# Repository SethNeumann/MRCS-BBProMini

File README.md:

# MRCS-BBProMini
## License: Creative Commons Attribution-NonCommercial-ShareAlike

A ProMini in a BBLeo form factor for use on MRCS cpNode

Initial proof of concept

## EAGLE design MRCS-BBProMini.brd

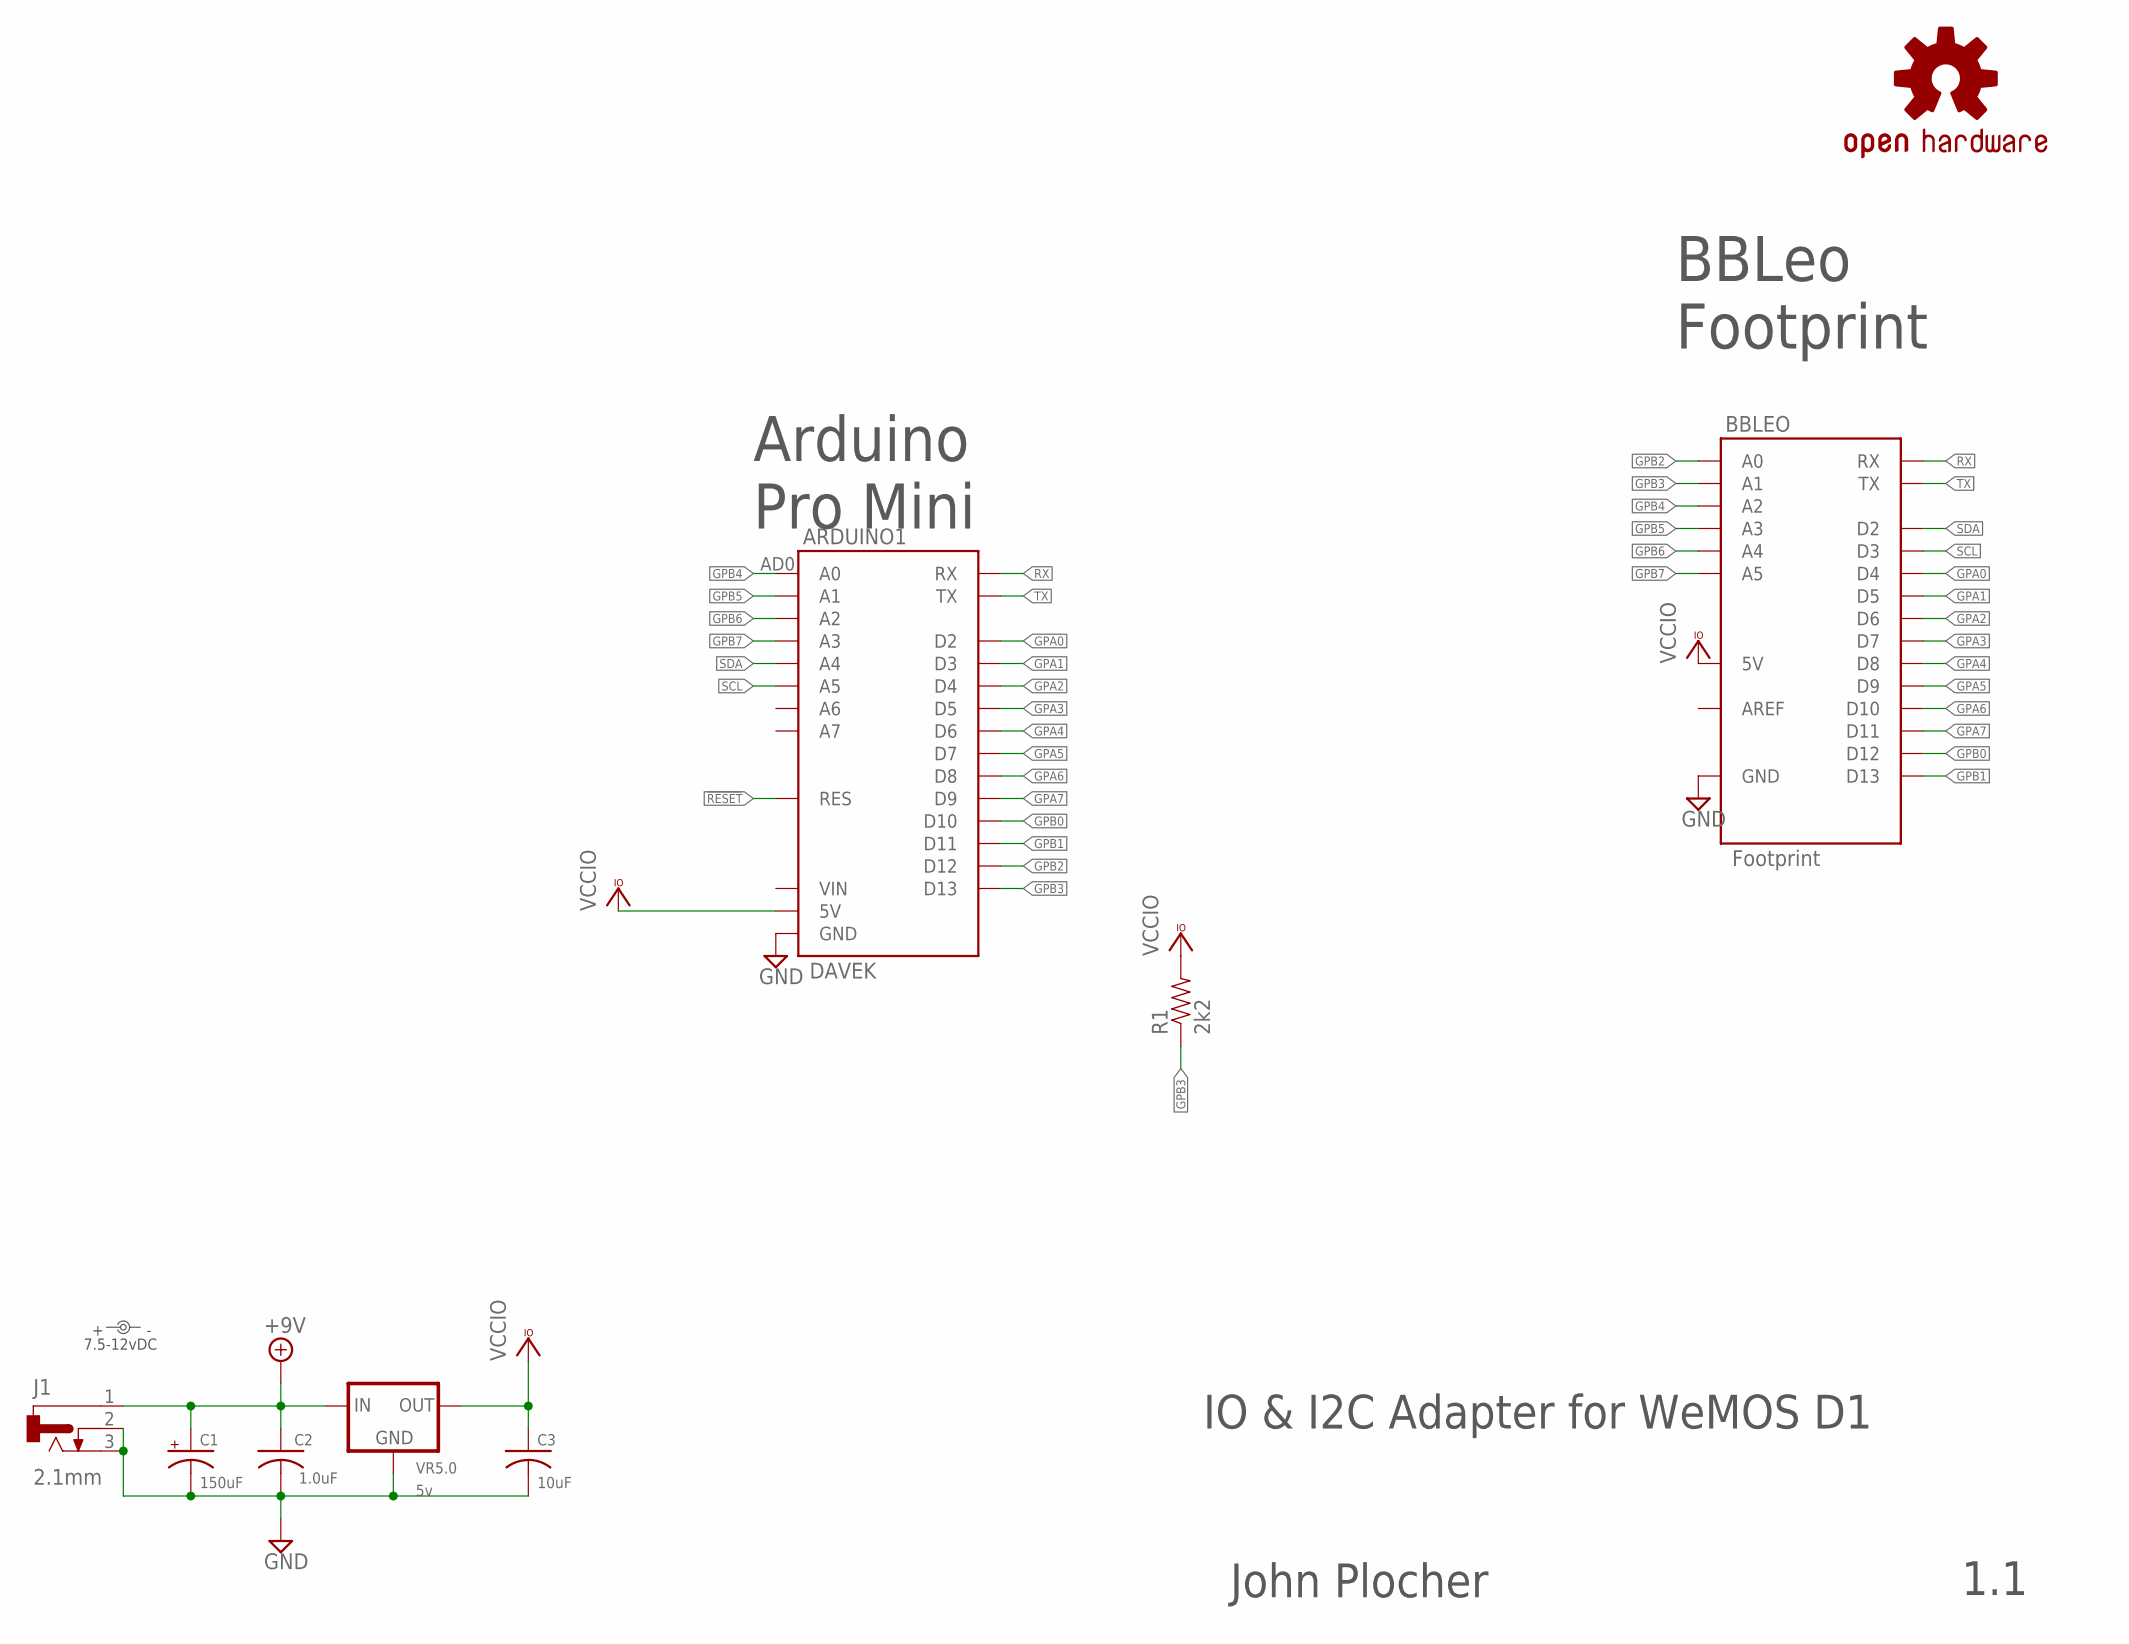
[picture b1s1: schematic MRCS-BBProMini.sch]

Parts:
ARDUINO1: DAVEK; ARDUINO_PRO_MINI_DAVEK
BBLEO: Footprint; ARDUINO-BBLEO
C1: 150uF; E5-10.5
C2: 1.0uF; C050-024X044
C3: 10uF; C050-024X044
J1: 2.1mm; DCJ0202
LABEL1: 7.5-12vDC; PWR_LABEL
OSHW1: OSHW; OSHW-LOGO-M
R1: 2k2; AXIAL-0.3-RES
VR5.0: 5v; TO-220-RA

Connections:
!RESET: ARDUINO1.RES, ARDUINO1.RES@1 (RES)
+9V: C1.+, C2.1, J1.1, VR5.0.IN
GND: ARDUINO1.GND@1 (GND), ARDUINO1.GND@2 (GND), ARDUINO1.GND@4 (GND), BBLEO.GND@0 (GND), BBLEO.GND@1 (GND), BBLEO.GND@2 (GND), BBLEO.GND@3 (GND), BBLEO.GND@4 (GND), C1.-, C2.2, C3.2, J1.2, J1.3, VR5.0.GND
GPA0: ARDUINO1.D2, BBLEO.D4
GPA1: ARDUINO1.D3, BBLEO.D5
GPA2: ARDUINO1.D4, BBLEO.D6
GPA3: ARDUINO1.D5, BBLEO.D7
GPA4: ARDUINO1.D6, BBLEO.D8
GPA5: ARDUINO1.D7, BBLEO.D9
GPA6: ARDUINO1.D8, BBLEO.D10
GPA7: ARDUINO1.D9, BBLEO.D11
GPB0: ARDUINO1.D10, BBLEO.D12
GPB1: ARDUINO1.D11, BBLEO.D13
GPB2: ARDUINO1.D12, BBLEO.A0
GPB3: ARDUINO1.D13, BBLEO.A1, R1.P$1 (1)
GPB4: ARDUINO1.AD0 (A0), BBLEO.A2
GPB5: ARDUINO1.AD1 (A1), BBLEO.A3
GPB6: ARDUINO1.AD2 (A2), BBLEO.A4
GPB7: ARDUINO1.AD3 (A3), BBLEO.A5
RX: ARDUINO1.RX, BBLEO.RX
SCL: ARDUINO1.AD5 (A5), BBLEO.SCL (D3)
SDA: ARDUINO1.AD4 (A4), BBLEO.SDA (D2)
TX: ARDUINO1.TX@1 (TX), BBLEO.TX
VCCIO: ARDUINO1.5V, BBLEO.+5V@1 (5V), BBLEO.+5V@2 (5V), BBLEO.+5V@3 (5V), BBLEO.+5V@4 (5V), C3.1, R1.P$2 (2), VR5.0.OUT

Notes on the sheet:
IO & I2C Adapter for WeMOS D1
John Plocher
1.1
Arduino Pro Mini
BBLeo Footprint

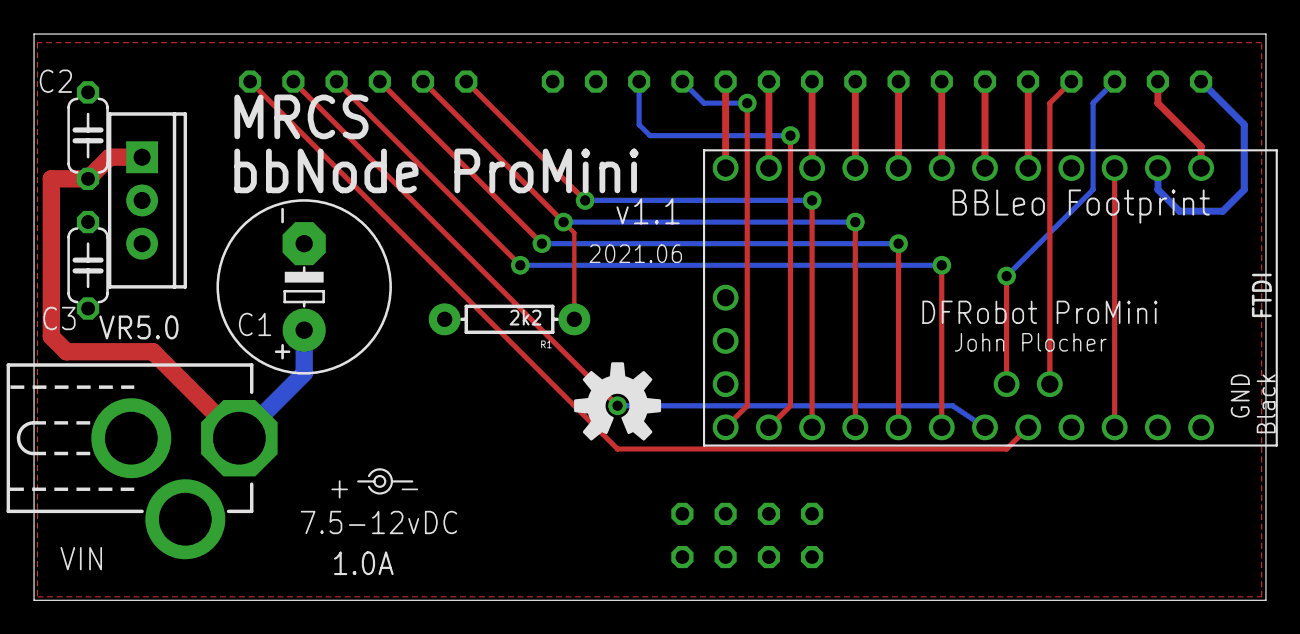
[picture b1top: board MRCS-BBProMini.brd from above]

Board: 2 copper layers, 72.4 x 33.3 mm, 10 parts (0 on the bottom side), 24 nets.

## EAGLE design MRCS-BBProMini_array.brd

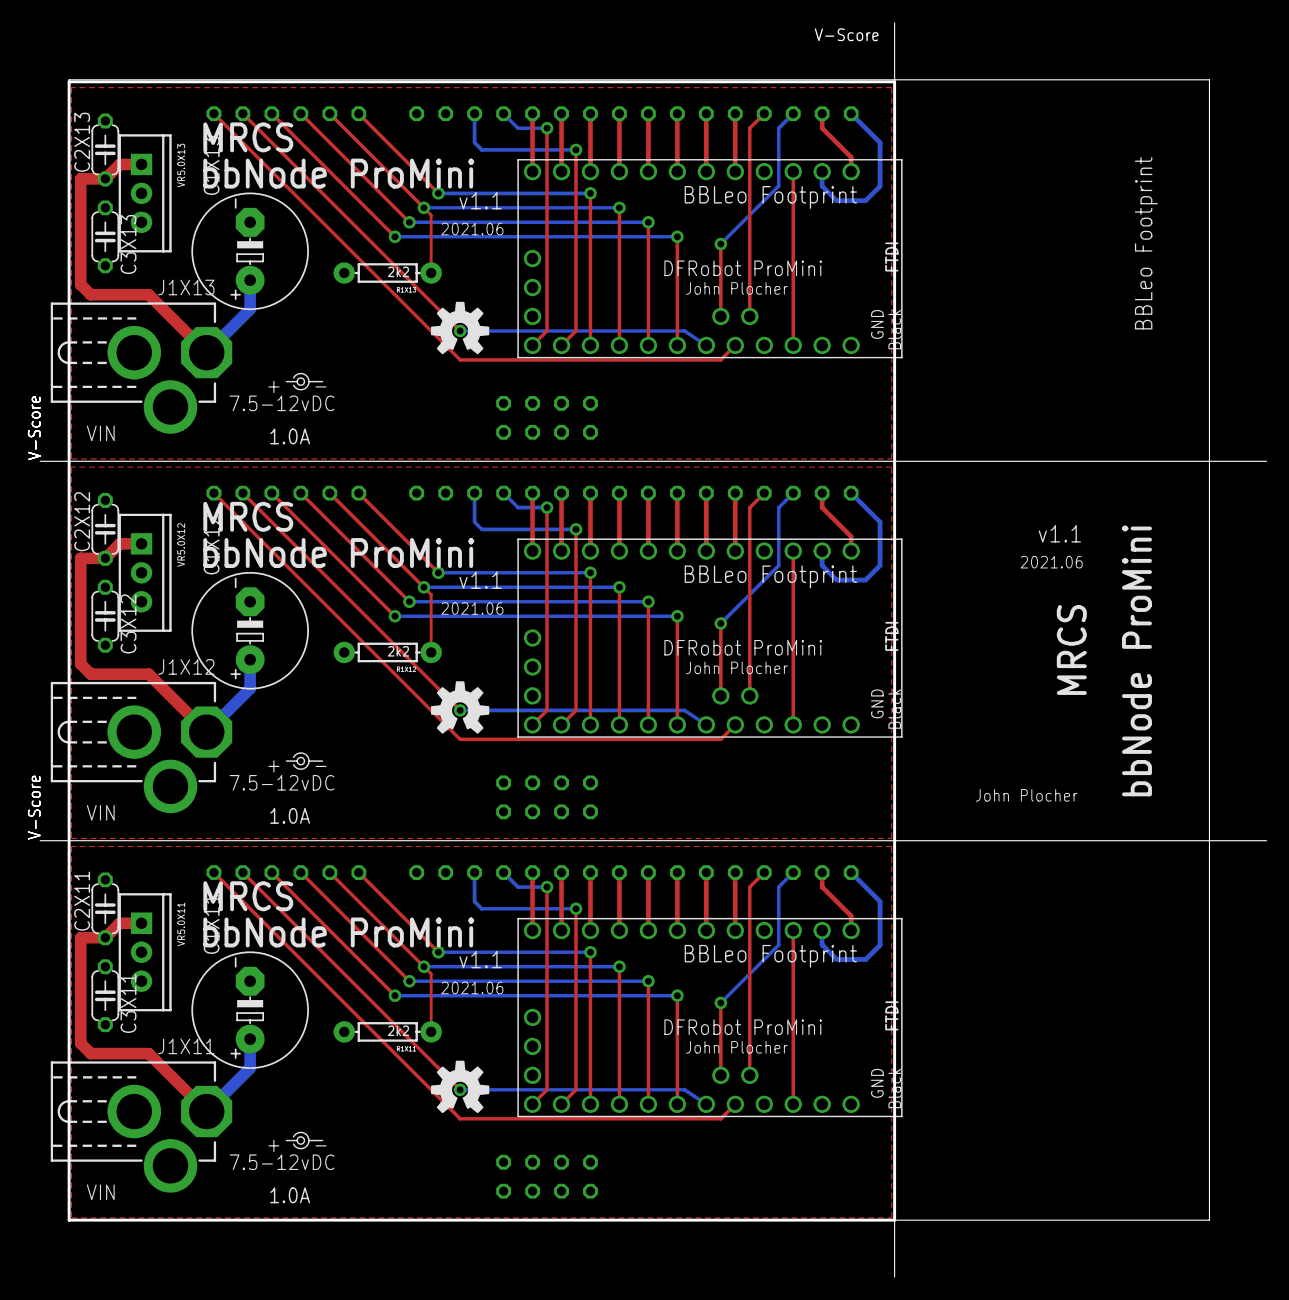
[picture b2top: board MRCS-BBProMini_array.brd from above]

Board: 2 copper layers, 108.8 x 109.7 mm, 30 parts (0 on the bottom side), 72 nets.

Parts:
ARDUINO1X11, ARDUINO1X12, ARDUINO1X13: DAVEK; ARDUINO_PRO_MINI_DAVEK
BBLEOX11, BBLEOX12, BBLEOX13: Footprint; ARDUINO-BBLEO
C1X11, C1X12, C1X13: 150uF; E5-10.5
C2X11, C2X12, C2X13: 1.0uF; C050-024X044
C3X11, C3X12, C3X13: 10uF; C050-024X044
J1X11, J1X12, J1X13: 2.1mm; DCJ0202
LABEL1X11, LABEL1X12, LABEL1X13: 7.5-12vDC; PWR_LABEL
OSHW1X11, OSHW1X12, OSHW1X13: OSHW; OSHW-LOGO-M
R1X11, R1X12, R1X13: 2k2; AXIAL-0.3-RES
VR5.0X11, VR5.0X12, VR5.0X13: 5v; TO-220-RA

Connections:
!RESETX11: ARDUINO1X11.RES, ARDUINO1X11.RES@1
!RESETX12: ARDUINO1X12.RES, ARDUINO1X12.RES@1
!RESETX13: ARDUINO1X13.RES, ARDUINO1X13.RES@1
+9VX11: C1X11.+, C2X11.1, J1X11.1, VR5.0X11.IN
+9VX12: C1X12.+, C2X12.1, J1X12.1, VR5.0X12.IN
+9VX13: C1X13.+, C2X13.1, J1X13.1, VR5.0X13.IN
GNDX11: ARDUINO1X11.GND@1, ARDUINO1X11.GND@2, ARDUINO1X11.GND@4, BBLEOX11.GND@0, BBLEOX11.GND@1, BBLEOX11.GND@2, BBLEOX11.GND@3, BBLEOX11.GND@4, C1X11.-, C2X11.2, C3X11.2, J1X11.2, J1X11.3, VR5.0X11.GND
GNDX12: ARDUINO1X12.GND@1, ARDUINO1X12.GND@2, ARDUINO1X12.GND@4, BBLEOX12.GND@0, BBLEOX12.GND@1, BBLEOX12.GND@2, BBLEOX12.GND@3, BBLEOX12.GND@4, C1X12.-, C2X12.2, C3X12.2, J1X12.2, J1X12.3, VR5.0X12.GND
GNDX13: ARDUINO1X13.GND@1, ARDUINO1X13.GND@2, ARDUINO1X13.GND@4, BBLEOX13.GND@0, BBLEOX13.GND@1, BBLEOX13.GND@2, BBLEOX13.GND@3, BBLEOX13.GND@4, C1X13.-, C2X13.2, C3X13.2, J1X13.2, J1X13.3, VR5.0X13.GND
GPA0X11: ARDUINO1X11.D2, BBLEOX11.D4
GPA0X12: ARDUINO1X12.D2, BBLEOX12.D4
GPA0X13: ARDUINO1X13.D2, BBLEOX13.D4
GPA1X11: ARDUINO1X11.D3, BBLEOX11.D5
GPA1X12: ARDUINO1X12.D3, BBLEOX12.D5
GPA1X13: ARDUINO1X13.D3, BBLEOX13.D5
GPA2X11: ARDUINO1X11.D4, BBLEOX11.D6
GPA2X12: ARDUINO1X12.D4, BBLEOX12.D6
GPA2X13: ARDUINO1X13.D4, BBLEOX13.D6
GPA3X11: ARDUINO1X11.D5, BBLEOX11.D7
GPA3X12: ARDUINO1X12.D5, BBLEOX12.D7
GPA3X13: ARDUINO1X13.D5, BBLEOX13.D7
GPA4X11: ARDUINO1X11.D6, BBLEOX11.D8
GPA4X12: ARDUINO1X12.D6, BBLEOX12.D8
GPA4X13: ARDUINO1X13.D6, BBLEOX13.D8
GPA5X11: ARDUINO1X11.D7, BBLEOX11.D9
GPA5X12: ARDUINO1X12.D7, BBLEOX12.D9
GPA5X13: ARDUINO1X13.D7, BBLEOX13.D9
GPA6X11: ARDUINO1X11.D8, BBLEOX11.D10
GPA6X12: ARDUINO1X12.D8, BBLEOX12.D10
GPA6X13: ARDUINO1X13.D8, BBLEOX13.D10
GPA7X11: ARDUINO1X11.D9, BBLEOX11.D11
GPA7X12: ARDUINO1X12.D9, BBLEOX12.D11
GPA7X13: ARDUINO1X13.D9, BBLEOX13.D11
GPB0X11: ARDUINO1X11.D10, BBLEOX11.D12
GPB0X12: ARDUINO1X12.D10, BBLEOX12.D12
GPB0X13: ARDUINO1X13.D10, BBLEOX13.D12
GPB1X11: ARDUINO1X11.D11, BBLEOX11.D13
GPB1X12: ARDUINO1X12.D11, BBLEOX12.D13
GPB1X13: ARDUINO1X13.D11, BBLEOX13.D13
GPB2X11: ARDUINO1X11.D12, BBLEOX11.A0
GPB2X12: ARDUINO1X12.D12, BBLEOX12.A0
GPB2X13: ARDUINO1X13.D12, BBLEOX13.A0
GPB3X11: ARDUINO1X11.D13, BBLEOX11.A1, R1X11.P$1
GPB3X12: ARDUINO1X12.D13, BBLEOX12.A1, R1X12.P$1
GPB3X13: ARDUINO1X13.D13, BBLEOX13.A1, R1X13.P$1
GPB4X11: ARDUINO1X11.AD0, BBLEOX11.A2
GPB4X12: ARDUINO1X12.AD0, BBLEOX12.A2
GPB4X13: ARDUINO1X13.AD0, BBLEOX13.A2
GPB5X11: ARDUINO1X11.AD1, BBLEOX11.A3
GPB5X12: ARDUINO1X12.AD1, BBLEOX12.A3
GPB5X13: ARDUINO1X13.AD1, BBLEOX13.A3
GPB6X11: ARDUINO1X11.AD2, BBLEOX11.A4
GPB6X12: ARDUINO1X12.AD2, BBLEOX12.A4
GPB6X13: ARDUINO1X13.AD2, BBLEOX13.A4
GPB7X11: ARDUINO1X11.AD3, BBLEOX11.A5
GPB7X12: ARDUINO1X12.AD3, BBLEOX12.A5
GPB7X13: ARDUINO1X13.AD3, BBLEOX13.A5
RXX11: ARDUINO1X11.RX, BBLEOX11.RX
RXX12: ARDUINO1X12.RX, BBLEOX12.RX
RXX13: ARDUINO1X13.RX, BBLEOX13.RX
SCLX11: ARDUINO1X11.AD5, BBLEOX11.SCL
SCLX12: ARDUINO1X12.AD5, BBLEOX12.SCL
SCLX13: ARDUINO1X13.AD5, BBLEOX13.SCL
SDAX11: ARDUINO1X11.AD4, BBLEOX11.SDA
SDAX12: ARDUINO1X12.AD4, BBLEOX12.SDA
SDAX13: ARDUINO1X13.AD4, BBLEOX13.SDA
TXX11: ARDUINO1X11.TX@1, BBLEOX11.TX
TXX12: ARDUINO1X12.TX@1, BBLEOX12.TX
TXX13: ARDUINO1X13.TX@1, BBLEOX13.TX
VCCIOX11: ARDUINO1X11.5V, BBLEOX11.+5V@1, BBLEOX11.+5V@2, BBLEOX11.+5V@3, BBLEOX11.+5V@4, C3X11.1, R1X11.P$2, VR5.0X11.OUT
VCCIOX12: ARDUINO1X12.5V, BBLEOX12.+5V@1, BBLEOX12.+5V@2, BBLEOX12.+5V@3, BBLEOX12.+5V@4, C3X12.1, R1X12.P$2, VR5.0X12.OUT
VCCIOX13: ARDUINO1X13.5V, BBLEOX13.+5V@1, BBLEOX13.+5V@2, BBLEOX13.+5V@3, BBLEOX13.+5V@4, C3X13.1, R1X13.P$2, VR5.0X13.OUT

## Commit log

2020-05-04 updated tags
2020-10-05 fixed silkscreen
2020-10-06 normalized values
2021-06-03 Add 2k2 pullup to pin13
2021-06-03 regen later 125

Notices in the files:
parts and their libraries:
SPCoast: http://freedomdefined.org/OSHW Creative Commons - Attribution - ShareAlike 3.0
